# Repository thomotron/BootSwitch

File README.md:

# BootSwitch
A serial-fed operating system selector switch for GRUB built on the ATTiny85.

This will listen for a phrase being sent in over serial and send a series of keystrokes back if it picks up the correct phrase.

# Why?
I run both Linux and Windows simultaneously on my main PC using GRUB2 as my bootloader.
By default GRUB will boot into Linux, but I have to wait ~10s from powering on before GRUB will let me choose my OS.
I'd much rather flip a switch and walk away while it boots into my OS of choice, so here we are.

# Requirements
This is built to run on an ATTiny85 connected to an MSI Z97S Krait Edition motherboard through the JCOM1 header. It might work with other boards, YMMV.

You'll need:
- An ATTiny25/45/85
- A PC with a serial port
- A MAX232 (optional, for logic level conversion)
- An ISP that can flash an AVR (I used a USBtinyISP)
- `make`
- `avrdude`
- `avr-gcc` and `avr-libc`

# Building
Open the `Firmware` directory and run `make`.

There are a couple of make targets:  
`make fuse`: Burns the fuses into the AVR  
`make flash`: Flashes the firmware  
`make clean`: Cleans up build artifacts

Chip-specific settings (fuses, clock speed, ISP, etc.) are defined in the makefile and should be modified to suit your environment.

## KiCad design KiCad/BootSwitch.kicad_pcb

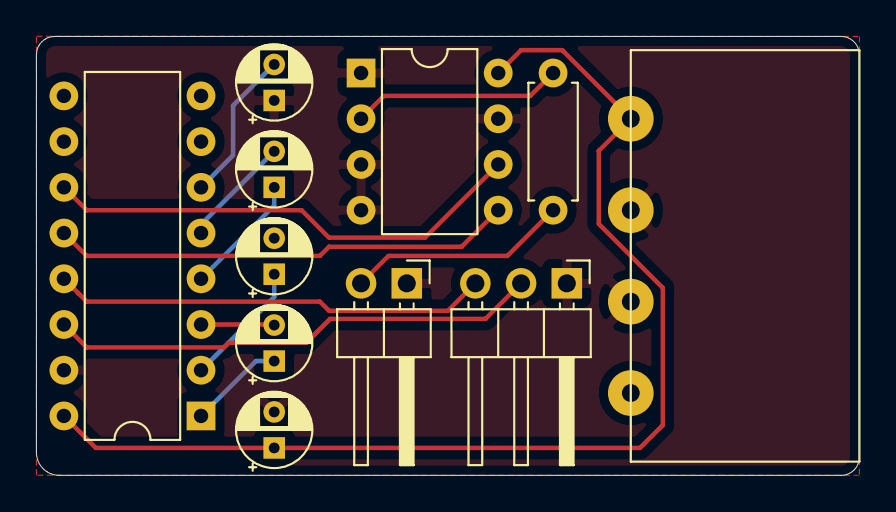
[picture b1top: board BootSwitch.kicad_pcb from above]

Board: 2 copper layers, 45.7 x 24.4 mm, 11 parts (0 on the bottom side), 14 nets.

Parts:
C1, C2, C3, C4, C5: 1uF; CP_Radial_D4.0mm_P2.00mm
J1: JCOM1; PinHeader_1x03_P2.54mm_Horizontal
J2: Molex 8981-P04; MOLEX_8981_4P_Horizontal
R1: 10k; R_Axial_DIN0207_L6.3mm_D2.5mm_P7.62mm_Horizontal
SW1: Case Switch; PinHeader_1x02_P2.54mm_Horizontal
U1: ATtiny85-20PU; DIP-8_W7.62mm
U2: MAX232; DIP-16_W7.62mm

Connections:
5v: C1.1, J2.4, U1.8, U2.16
Earth: C1.2, C2.2, C5.1, J1.1, J2.2, J2.3, SW1.1, U1.1, U1.3, U1.4, U1.7, U2.15
unnamed: C2.1, U2.2
unnamed: C3.1, U2.1
unnamed: C3.2, U2.3
unnamed: C4.1, U2.4
unnamed: C4.2, U2.5
unnamed: C5.2, U2.6
unnamed: J1.2, U2.14
unnamed: J1.3, U2.13
unnamed: R1.1, SW1.2
unnamed: R1.2, U1.2
unnamed: U1.5, U2.12
unnamed: U1.6, U2.11

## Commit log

2021-04-25 Initial commit 🎉
2021-04-26 First implementation
2021-04-26 Fix incorrect clock prescaler
    Clock was set to prescale down by a factor of 8 to 1MHz, causing communication issues.
    Fixed by disabling the prescaler.
2021-04-26 Use macro high/low definitions
2021-04-26 Define phrase as const
2021-04-26 Add schematic
2021-04-28 Fixed issues and got a working implementation
    Added debug section to view current buffer state
    Fixed send/receive shifting signed chars, causing send/receive to stop
    early
    Fixed buffer only using one iterator, therefore never matching unless
    the match was from the start of the buffer
2021-05-08 Use Timer0 for rx bit timing
2021-05-10 Use pinterrupts to sync with the start bit
    Finally got a working implementation without absurd timing issues
2021-05-13 Clean up firmware
2021-05-13 Update schematic
2021-05-17 Revise PCB for production
2021-05-17 Add KiCad schematic and xess parts lib
